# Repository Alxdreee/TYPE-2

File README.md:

# TYPE-2 — Open-Source Polyphonic Touch Synthesizer (ESP32-S3)

**Firmware:** v1.6.0 · **Hardware:** V2 (released) — V3 full-SMT (in development)
**Author:** Alexandre Esnard

The TYPE-2 is an open-source, touch-capacitive polyphonic synthesizer built around the ESP32-S3. Its DSP engine, written from scratch in C++, combines fast polynomial saturation, a dual-rate processing architecture and analog-modeled filters to deliver a rich, expressive sound from a ~€35 instrument.

> Featured on **XDA Developers** (twice) and documented in a full **Instructables** Featured build guide — see [Press & Community](#press--community).

## Core Features

* **Hybrid DSP Engine:** 7-voice polyphony, fast polynomial saturation and dual-rate architecture.
* **Signal Chain:** Factorized 24dB/Oct Trapezoidal SVF Filter, Tube Overdrive, analog slop and Studio Digital Delay.
* **User Interface:** Cylindrical rotary menu, responsive topological grid visualization, preset management.
* **Connectivity:** Composite USB Device (Native USB MIDI Out + USB PCM Audio Stream) for direct DAW integration.

## Hardware Versions

| Version | Description | Status |
|---|---|---|
| **V1** | Off-the-shelf modules, hand wiring, copper-tape touch keys | Released |
| **V2** | Custom motherboard PCB carrying the modules (ESP32-S3-DevKitC-1, DAC, OLED, MPR121) | Released, Gerbers in `hardware/` |
| **V3** | Fully SMT two-board design, factory-assembled, PCB touch pads |In development, prototype stage |

### V3 — Fully SMT, factory-assembled design

V3 replaces the module stack with two custom boards designed in KiCad for turnkey PCB assembly:

* **Backplate:** ESP32-S3-WROOM-1-N16R8, PCM5102A DAC, native USB-C (programming, MIDI, audio) with ESD protection (USBLC6-2SC6), separate low-noise LDO (LP5907) for the analog audio rail, 3.5mm line output.
* **Frontplate:** 2x MPR121 (QFN) on two independent I2C buses, 24 touch keys etched directly on the PCB, no more copper tape.
* **Board-to-board:** single 2x4 header, no wiring at all.
* **Remaining hand-soldered parts:** OLED display, rotary encoder, navigation button, headers.

**Goal:** production-ready Gerber, BOM and CPL files (with LCSC part numbers, Basic parts prioritized) so that anyone can order an assembled TYPE-2 in a few clicks. These files will be published once the prototype is validated.

### V2 Hardware BOM

* ESP32-S3-DevKitC-1 board, 44 pins (ESP32-S3-WROOM-1 N16R8: 16MB Flash, 8MB OPI PSRAM **required**)
* PCM5102A I2S DAC Module
* SSD1306 128x64 I2C OLED Display
* KY-040 Rotary Encoder
* 1x Tactile Navigation Button
* 2x MPR121 I2C Capacitive Touch Sensors
* TYPE-2 V2 motherboard PCB (or breadboard + copper tape for V1)

> **V2 ESP32-S3 FORM FACTOR NOTICE:**
> The V2 PCB is routed for the standard **ESP32-S3-DevKitC-1** form factor (**44 pins, 2x22 headers, 2.54mm pitch**).
> Do **not** use 38-pin or 30-pin ESP32-S3 boards: their power and GPIO pinouts will not match and will cause short circuits. Always check your board against [`hardware/wiring_diagram.md`](./hardware/wiring_diagram.md) and [`hardware/Type2_v2.kicad_sch`](./hardware/Type2_v2.kicad_sch) before soldering.

## Repository Structure

* `enclosure/` : 3D models and CAD files for the synthesizer casing.
* `firmware/` : Main `TYPE2.ino` firmware and the `type2_audio_bridge.py` USB audio streaming script.
* `hardware/` : V2 KiCad project, wiring diagram and production-ready `Type2_v2_Gerber.zip`.
* `[hardware/V3/]` : V3 KiCad projects (backplate + frontplate) — work in progress.

## Setup & Installation

1. **IDE Setup:** Install the Arduino IDE or PlatformIO with ESP32 board support.
2. **Compiler Settings:**
   * **USB Mode:** USB-OTG (TinyUSB) or Hardware CDC and JTAG
   * **USB CDC On Boot:** Enabled
   * **CPU Frequency:** 240MHz (WiFi)
   * **Flash Mode:** QIO 80MHz
   * **Flash Size:** 16MB (128Mb)
   * **Partition Scheme:** 16M Flash (3MB APP/9.9MB FATFS)
   * **PSRAM:** OPI PSRAM
   * **Upload Speed:** 115200
3. **Libraries:** Install `Adafruit GFX`, `Adafruit SSD1306` and `Adafruit MPR121`.
4. **Wiring (V1/V2):** Follow `hardware/wiring_diagram.md` for the I2S, I2C and GPIO connections.
5. **USB Audio Bridge (optional):** Run `firmware/type2_audio_bridge.py` on your computer to stream audio over USB.

## Press & Community

* **Instructables:** [DIY €35 Polyphonic Synthesizer — the TYPE-2](https://www.instructables.com/DIY-35-Polyphonic-Synthesizer-the-TYPE-2/)
* **Reddit:** [Development log](https://www.reddit.com/user/Alxdreee/submitted/)
* **XDA Developers:** [Someone turned their ESP32 into a touch-activated polyphonic synthesizer](https://www.xda-developers.com/someone-turned-their-esp32-into-a-touch-activated-polyphonic-synthesizer/)
* **XDA Developers:** [This open-source ESP32 touch synth just got a massive upgrade](https://www.xda-developers.com/this-open-source-esp32-touch-synth-just-got-a-massive-upgrade-and-its-only-35-to-make/)

## Manufacturing & Acknowledgements

The V2 Gerber files are standard and can be ordered from any PCB manufacturer.
Thanks to **PCBWay** for sponsoring the manufacturing of the TYPE-2 V2 boards.

## Roadmap

- [x] 7-voice polyphonic DSP engine
- [x] Tube overdrive, analog slop and delay effects
- [x] Real-time topological grid UI and hierarchical menu
- [x] Firmware optimization and improved menu navigation
- [x] Preset creation menu
- [x] External MIDI communication (USB/Serial)
- [x] Direct USB PCM audio streaming (Python bridge)
- [x] Custom PCB design (V2)
- [ ] **V3 full-SMT two-board design** (schematics done, layout & prototype in progress)
- [ ] V3 one-click assembly files (Gerber / BOM / CPL)
- [ ] Enclosure for V3
- [ ] ESP32 Bluetooth integration
- [ ] Battery management for portable use

## Links & Contact

* [GitHub](https://github.com/Alxdreee)
* [YouTube](https://www.youtube.com/@alexndreee)
* [LinkedIn](https://www.linkedin.com/in/alexandreesnard/)
* [Instructables](https://www.instructables.com/DIY-35-Polyphonic-Synthesizer-the-TYPE-2/)
* Contact / collaborations: alxdreee.esn@gmail.com

## Support the Project

TYPE-2 is developed entirely on my own, in my spare time, as a student. If you like the project, you can support it here:

[Buy Me a Coffee](https://buymeacoffee.com/alexandre.esnard)

## License & Copyright

This project is a community initiative for makers and synthesizer enthusiasts.

* **Community Use:** You are free to study, modify and build upon this project for personal use.
* **Commercial Restriction:** Commercial resale of this project, its code, or hardware derivatives based directly on this architecture is prohibited.
* **Patent Restriction:** No patents, trademarks or restrictive IP rights may be filed on this work or its derivatives.

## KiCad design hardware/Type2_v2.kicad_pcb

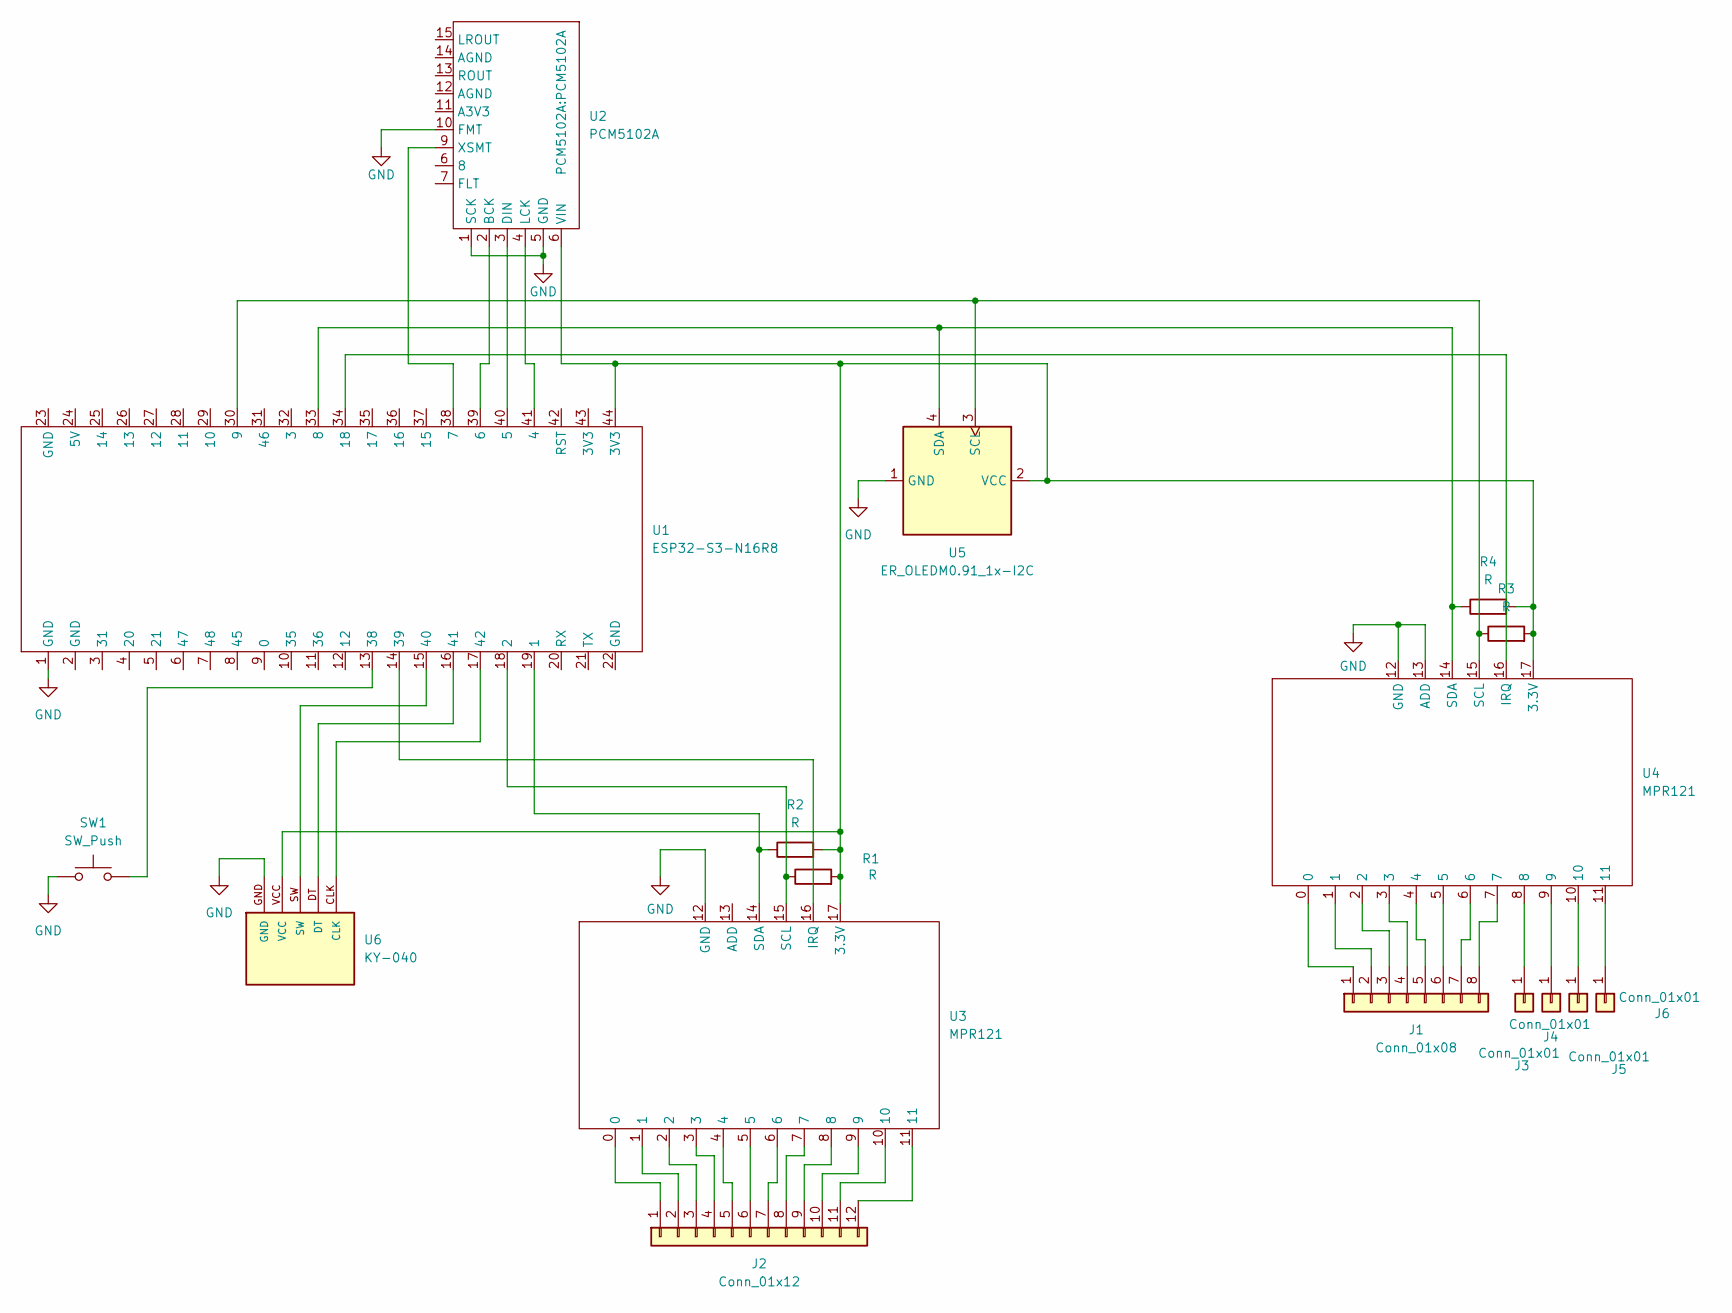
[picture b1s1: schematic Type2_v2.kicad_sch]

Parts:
J1: Conn_01x08; Pad_Qualite_8
J2: Conn_01x12; Pad_Accord_12
J3, J4, J5, J6: Conn_01x01; Touche capacitive
R1, R2, R3, R4: R; R_Axial_DIN0207_L6.3mm_D2.5mm_P10.16mm_Horizontal
SW1: SW_Push; SW_PUSH-12mm
U1: ESP32-S3-N16R8; Sans titre
U2: PCM5102A
U3, U4: MPR121
U5: ER_OLEDM0.91_1x-I2C
U6: KY-040; KY-040-PORT

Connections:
GND: SW1.1, U1.1 (GND), U2.1 (SCK), U2.5 (GND), U2.10 (FMT), U3.12 (GND), U4.12 (GND), U4.13 (ADD), U5.1 (GND), U6.GND
unnamed: J1.1, U4.0
unnamed: J1.2, U4.1
unnamed: J1.3, U4.2
unnamed: J1.4, U4.3
unnamed: J1.5, U4.4
unnamed: J1.6, U4.5
unnamed: J1.7, U4.6
unnamed: J1.8, U4.7
unnamed: J2.1, U3.0
unnamed: J2.2, U3.1
unnamed: J2.3, U3.2
unnamed: J2.4, U3.3
unnamed: J2.5, U3.4
unnamed: J2.6, U3.5
unnamed: J2.7, U3.6
unnamed: J2.8, U3.7
unnamed: J2.9, U3.8
unnamed: J2.10, U3.9
unnamed: J2.11, U3.10
unnamed: J2.12, U3.11
unnamed: J3.1 (Pin_1_1), U4.8
unnamed: J4.1 (Pin_1_1), U4.9
unnamed: J5.1 (Pin_1_1), U4.10
unnamed: J6.1 (Pin_1_1), U4.11
unnamed: R2.1, U1.19 (1), U3.14 (SDA)
unnamed: R1.1, U1.18 (2), U3.15 (SCL)
unnamed: U1.41 (4), U2.4 (LCK)
unnamed: U1.40 (5), U2.3 (DIN)
unnamed: U1.39 (6), U2.2 (BCK)
unnamed: U1.38 (7), U2.9 (XSMT)
unnamed: R4.1, U1.33 (8), U4.14 (SDA), U5.4 (SDA)
unnamed: R3.1, U1.30 (9), U4.15 (SCL), U5.3 (SCL)
unnamed: U1.34 (18), U4.16 (IRQ)
unnamed: SW1.2, U1.13 (38)
unnamed: U1.14 (39), U3.16 (IRQ)
unnamed: U1.15 (40), U6.SW
unnamed: U1.16 (41), U6.DT
unnamed: U1.17 (42), U6.CLK
unnamed: R1.2, R2.2, R3.2, R4.2, U1.44 (3V3), U2.6 (VIN), U3.17 (3.3V), U4.17 (3.3V), U5.2 (VCC), U6.VCC

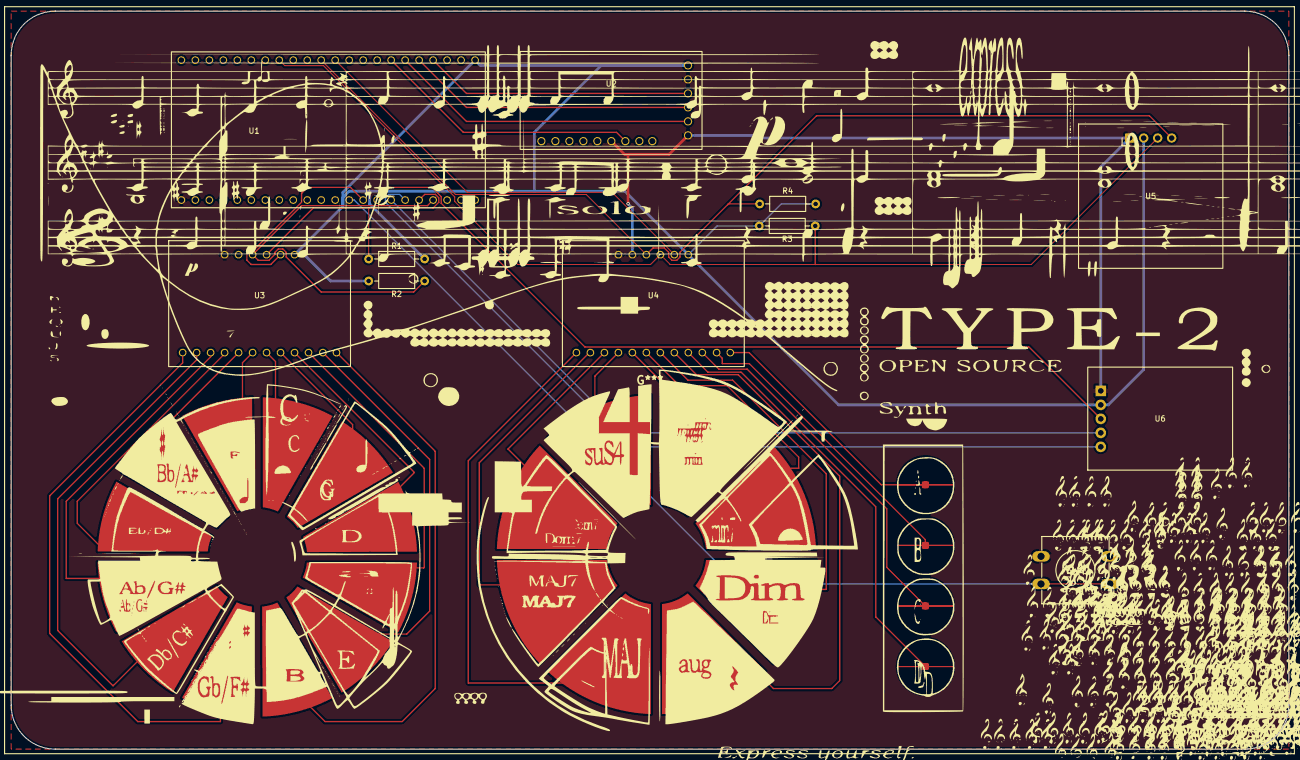
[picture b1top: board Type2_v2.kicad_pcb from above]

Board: 2 copper layers, 232.0 x 134.0 mm, 17 parts (0 on the bottom side), 40 nets.
